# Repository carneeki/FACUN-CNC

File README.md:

# FACUN-CNC
It's not FANUC. It's FUCAN!

FUCAN CNC is a collection of circuits designed to enable connection of an
Arduino, probably running Grbl, to the "real world", that is, your stepper
controllers, limit switches, push buttons and pendants (if applicable), and so
on.

Developed by an impoverished university student, it is designed to be budget
conscious, whilst minimising compromises on things that are nice to have. One
example is that all logic components are in DIP form factor so they can be
socketed and easily replaced in the event that the magic smoke escapes a
component.

## TRI-LIMIT-INTERFACE
TRI-LIMIT-INTERFACE is a 3 axis limit switch debounce and logical OR board.
Because we often have limit switches at each end of our axis limits, this
handles debouncing both ends, and sending a single clean signal to the Arduino.

Grbl has some debounce routines in it, but having this board enables changing to
other systems that may not have debouncing built in.

## LIMIT-INTERFACE
LIMIT-INTERFACE is a single axis, strip board version of the 3 axis board. Not
everyone can fab a PCB, and not everyone can afford to have the large 3 axis
board professionally fabbed. The strip board version can be easily made (and
tripled) while getting started. Once you are up and running, you should be able
to route the TRI version if you are so inclined.

## PUSHBUTTON-DEBOUNCE
PUSHBUTTON-DEBOUNCE is a board for debouncing pushbutton switches.

## ArduinoMiniPro Breakout
The Arduino Mini Pro is a really neat little board. It takes an Arduino and puts
it into a wide DIP array.

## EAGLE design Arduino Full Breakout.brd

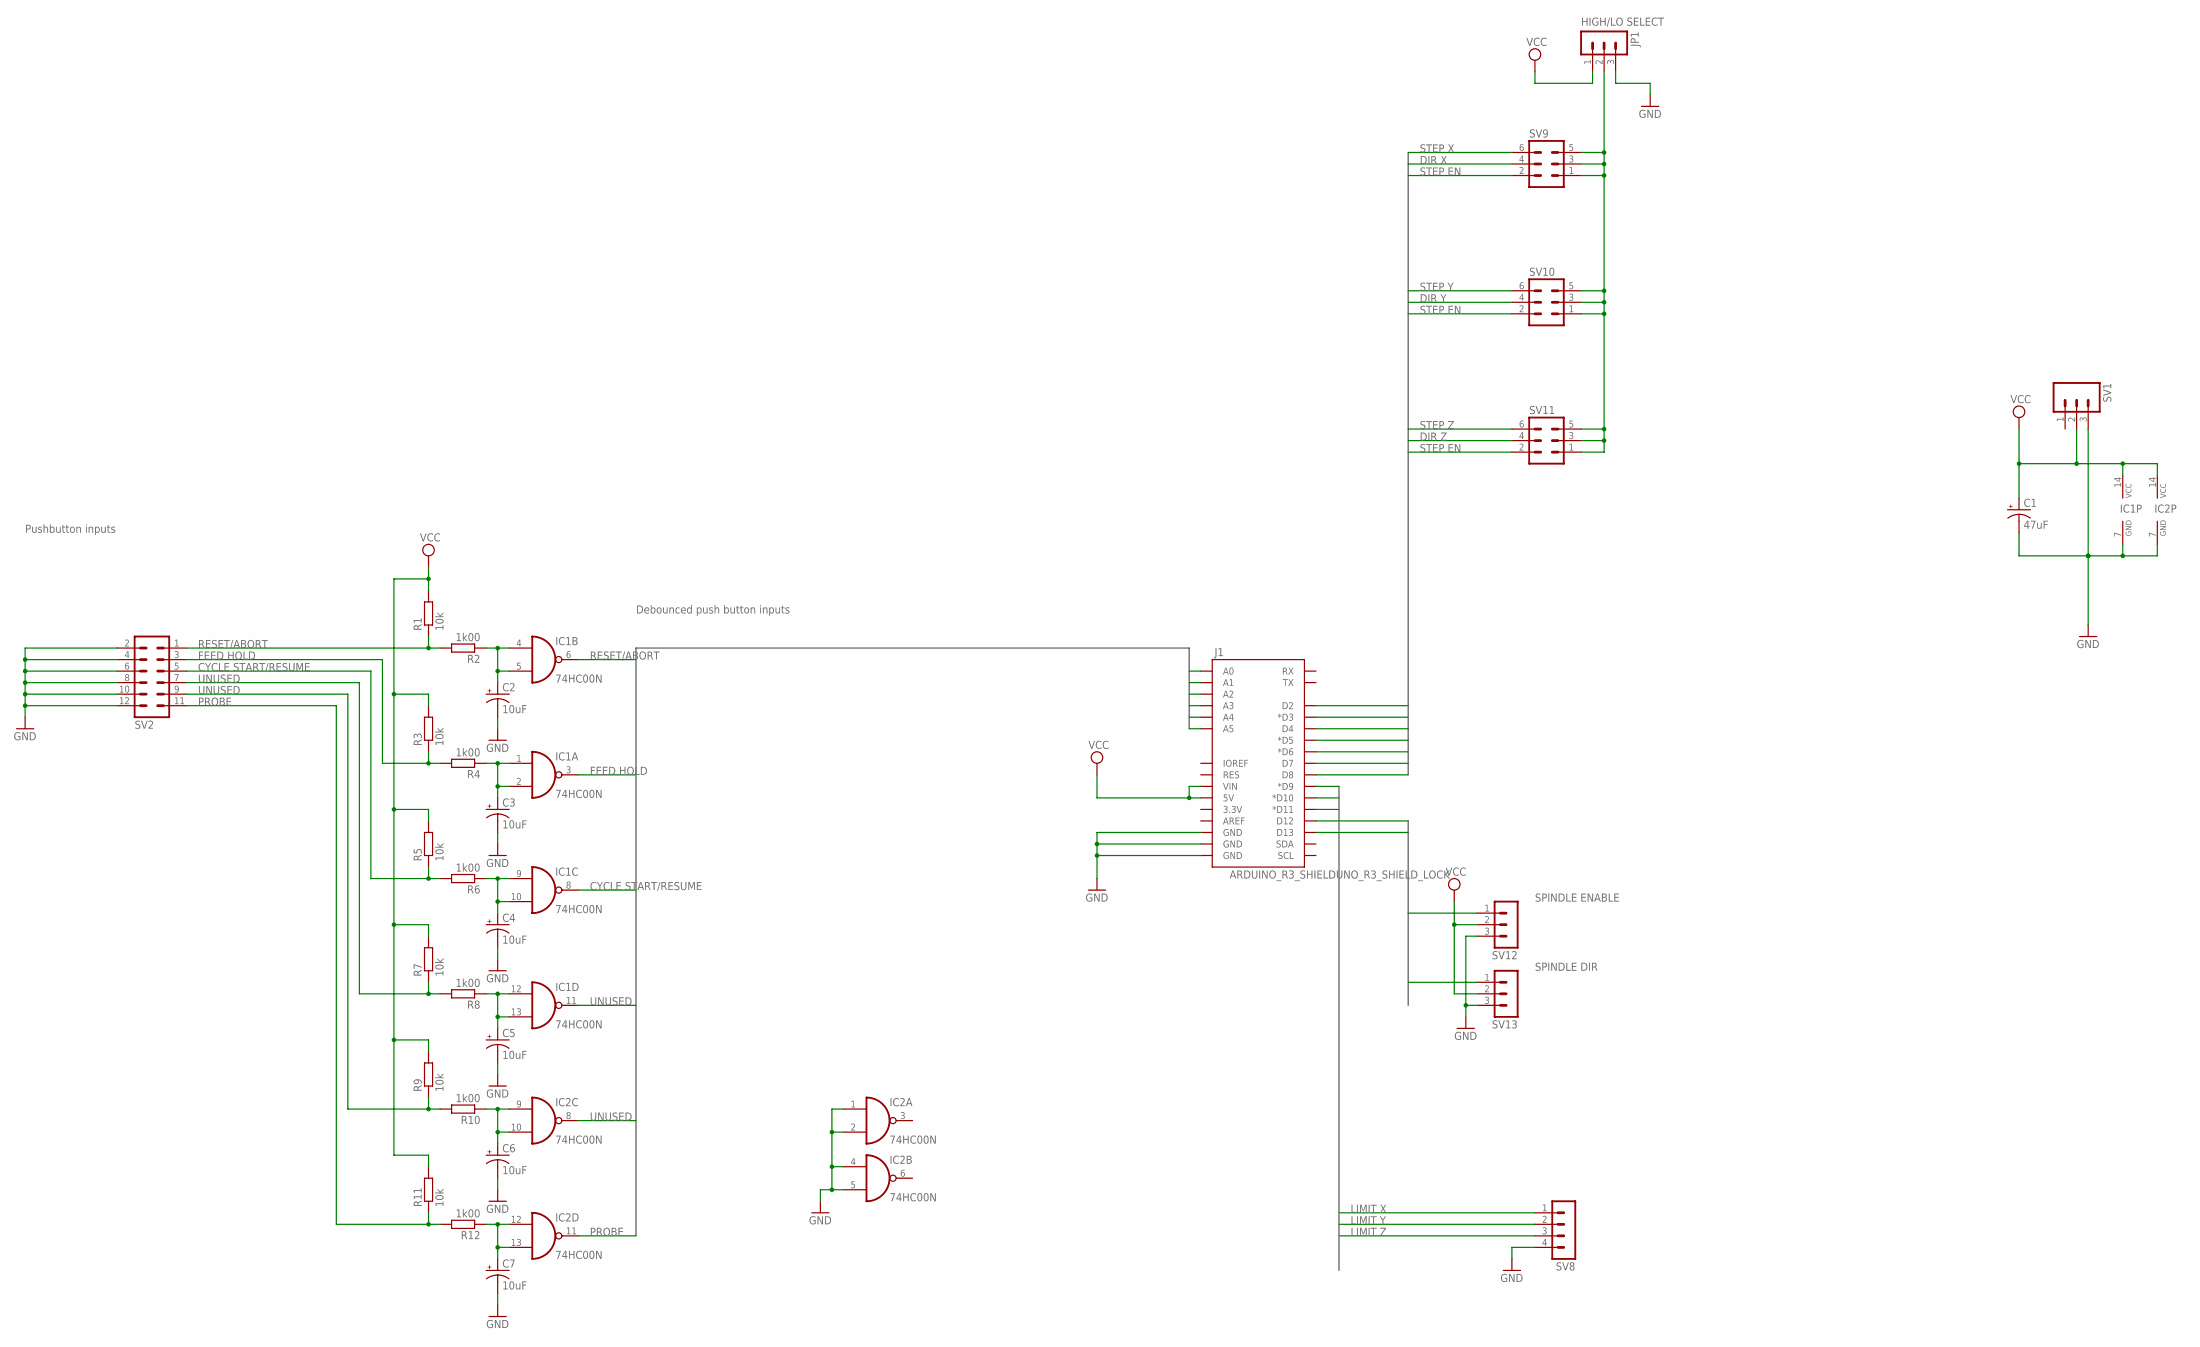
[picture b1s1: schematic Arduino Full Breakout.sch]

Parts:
C1: 47uF; CPOL-RADIAL-10UF-25V
C2, C3, C4, C5, C6, C7: 10uF; CPOL-RADIAL-10UF-25V
IC1, IC2: 74HC00N; DIL14
J1: ARDUINO_R3_SHIELDUNO_R3_SHIELD_LOCK; UNO_R3_SHIELD_LOCK
JP1: MA03-1
R1, R11: 10k; 0207/5V
R2, R4, R6, R8, R10, R12: 1k00; 0207/7
R3, R9: 10k; 0207/7
R5, R7: 10k; 0207/10
SV1: M03-SCREW-5MM; SCREWTERMINAL-5MM-3
SV2: MA06-2
SV8: MA04-1
SV9, SV10, SV11: MA03-2
SV12, SV13: MA03-1

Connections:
BUTTONS0: IC1.6 (O), J1.A0
BUTTONS1: IC1.3 (O), J1.A1
BUTTONS2: IC1.8 (O), J1.A2
BUTTONS3: IC1.11 (O), J1.A3
BUTTONS4: IC2.8 (O), J1.A4
BUTTONS5: IC2.11 (O), J1.A5
GND: C1.2 (-), C2.2 (-), C3.2 (-), C4.2 (-), C5.2 (-), C6.2 (-), C7.2 (-), IC1.7 (GND), IC2.1 (I0), IC2.2 (I1), IC2.4 (I0), IC2.5 (I1), IC2.7 (GND), J1.GND@0 (GND), J1.GND@1 (GND), J1.GND@2 (GND), JP1.3, SV1.3, SV2.2, SV2.4, SV2.6, SV2.8, SV2.10, SV2.12, SV8.4, SV12.3, SV13.3
LIMITS0: J1.D9 (*D9), SV8.1
LIMITS1: J1.D10 (*D10), SV8.2
LIMITS2: J1.D11 (*D11), SV8.3
unnamed: JP1.2, SV9.1, SV9.3, SV9.5, SV10.1, SV10.3, SV10.5, SV11.1, SV11.3, SV11.5
unnamed: C2.1 (+), IC1.4 (I0), IC1.5 (I1), R2.1
unnamed: R1.1, R2.2, SV2.1
unnamed: C3.1 (+), IC1.1 (I0), IC1.2 (I1), R4.1
unnamed: R3.1, R4.2, SV2.3
unnamed: C4.1 (+), IC1.9 (I0), IC1.10 (I1), R6.1
unnamed: R5.1, R6.2, SV2.5
unnamed: C5.1 (+), IC1.12 (I0), IC1.13 (I1), R8.1
unnamed: R7.1, R8.2, SV2.7
unnamed: C6.1 (+), IC2.9 (I0), IC2.10 (I1), R10.1
unnamed: R9.1, R10.2, SV2.9
unnamed: C7.1 (+), IC2.12 (I0), IC2.13 (I1), R12.1
unnamed: R11.1, R12.2, SV2.11
SPINDLE0: J1.D12, SV12.1
SPINDLE1: J1.D13, SV13.1
STEP0: J1.D2, SV9.6
STEP1: J1.D3 (*D3), SV10.6
STEP2: J1.D4, SV11.6
STEP3: J1.D5 (*D5), SV9.4
STEP4: J1.D6 (*D6), SV10.4
STEP5: J1.D7, SV11.4
STEP6: J1.D8, SV9.2, SV10.2, SV11.2
VCC: C1.1 (+), IC1.14 (VCC), IC2.14 (VCC), J1.VIN, JP1.1, R1.2, R3.2, R5.2, R7.2, R9.2, R11.2, SV1.2, SV12.2, SV13.2

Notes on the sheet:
RESET/ABORT
FEED HOLD
CYCLE START/RESUME
UNUSED
PROBE
SPINDLE DIR
SPINDLE ENABLE
LIMIT X
LIMIT Y
LIMIT Z
STEP X
STEP Y
HIGH/LO SELECT
DIR X
DIR Y
STEP Z
DIR Z
STEP EN
Debounced push button inputs
Pushbutton inputs

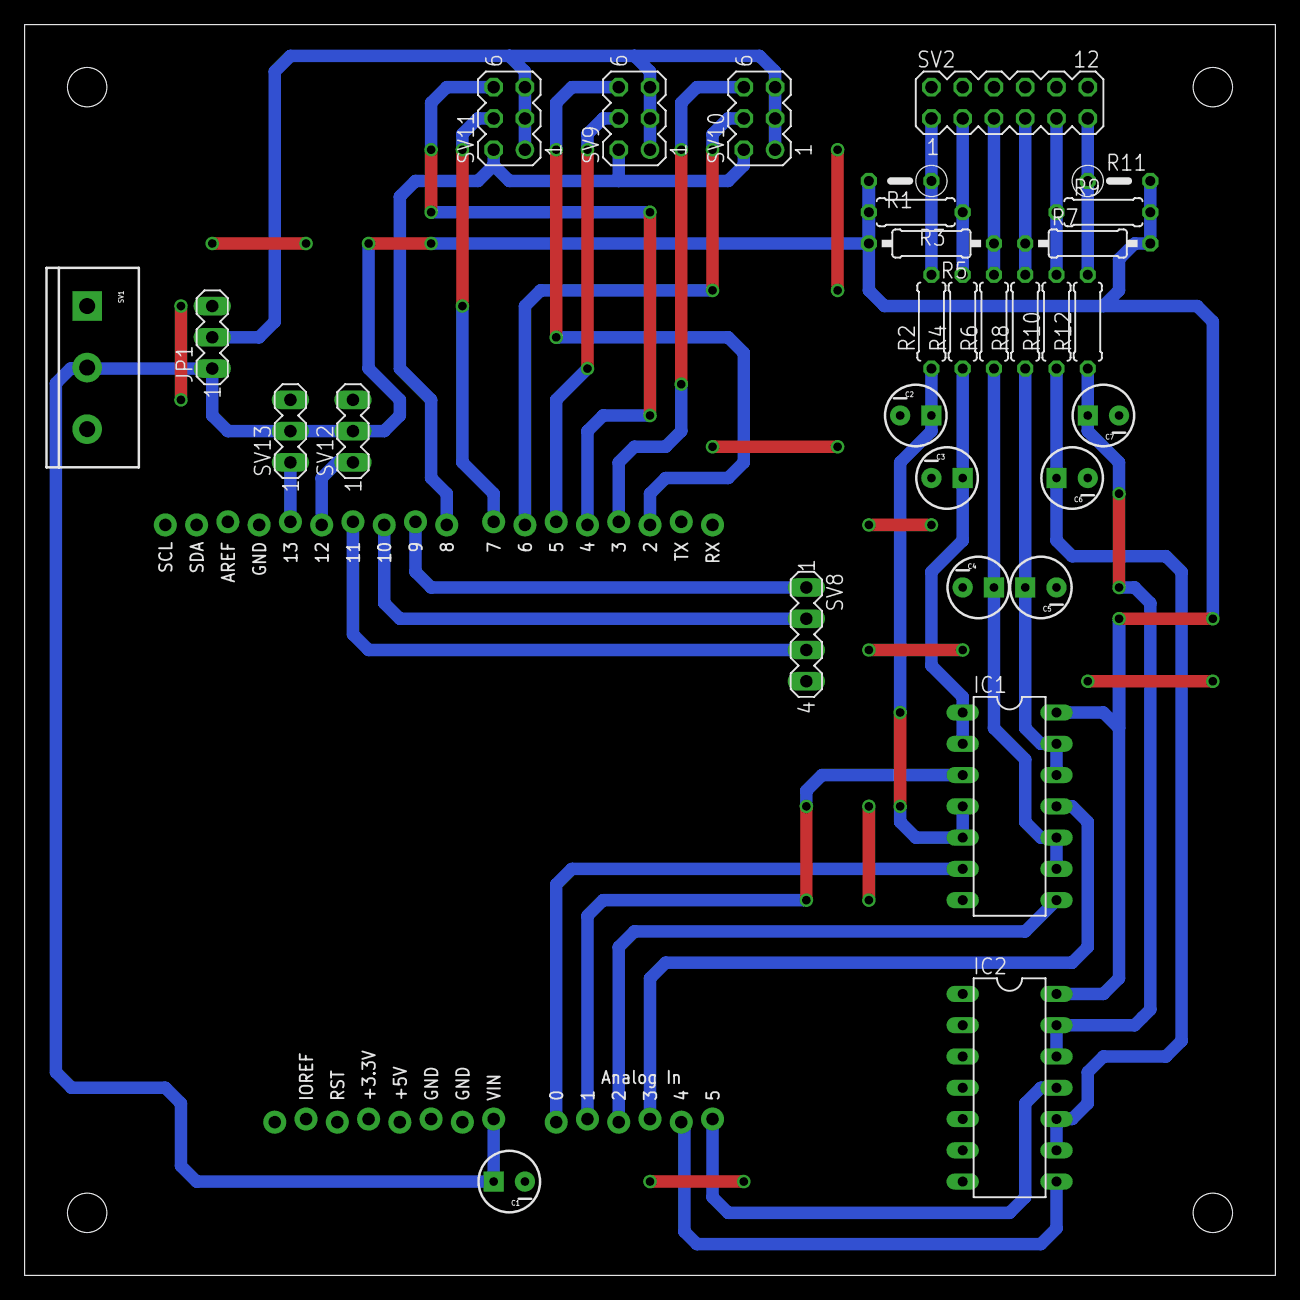
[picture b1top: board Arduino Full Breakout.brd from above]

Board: 2 copper layers, 101.6 x 101.6 mm, 31 parts (0 on the bottom side), 33 nets.

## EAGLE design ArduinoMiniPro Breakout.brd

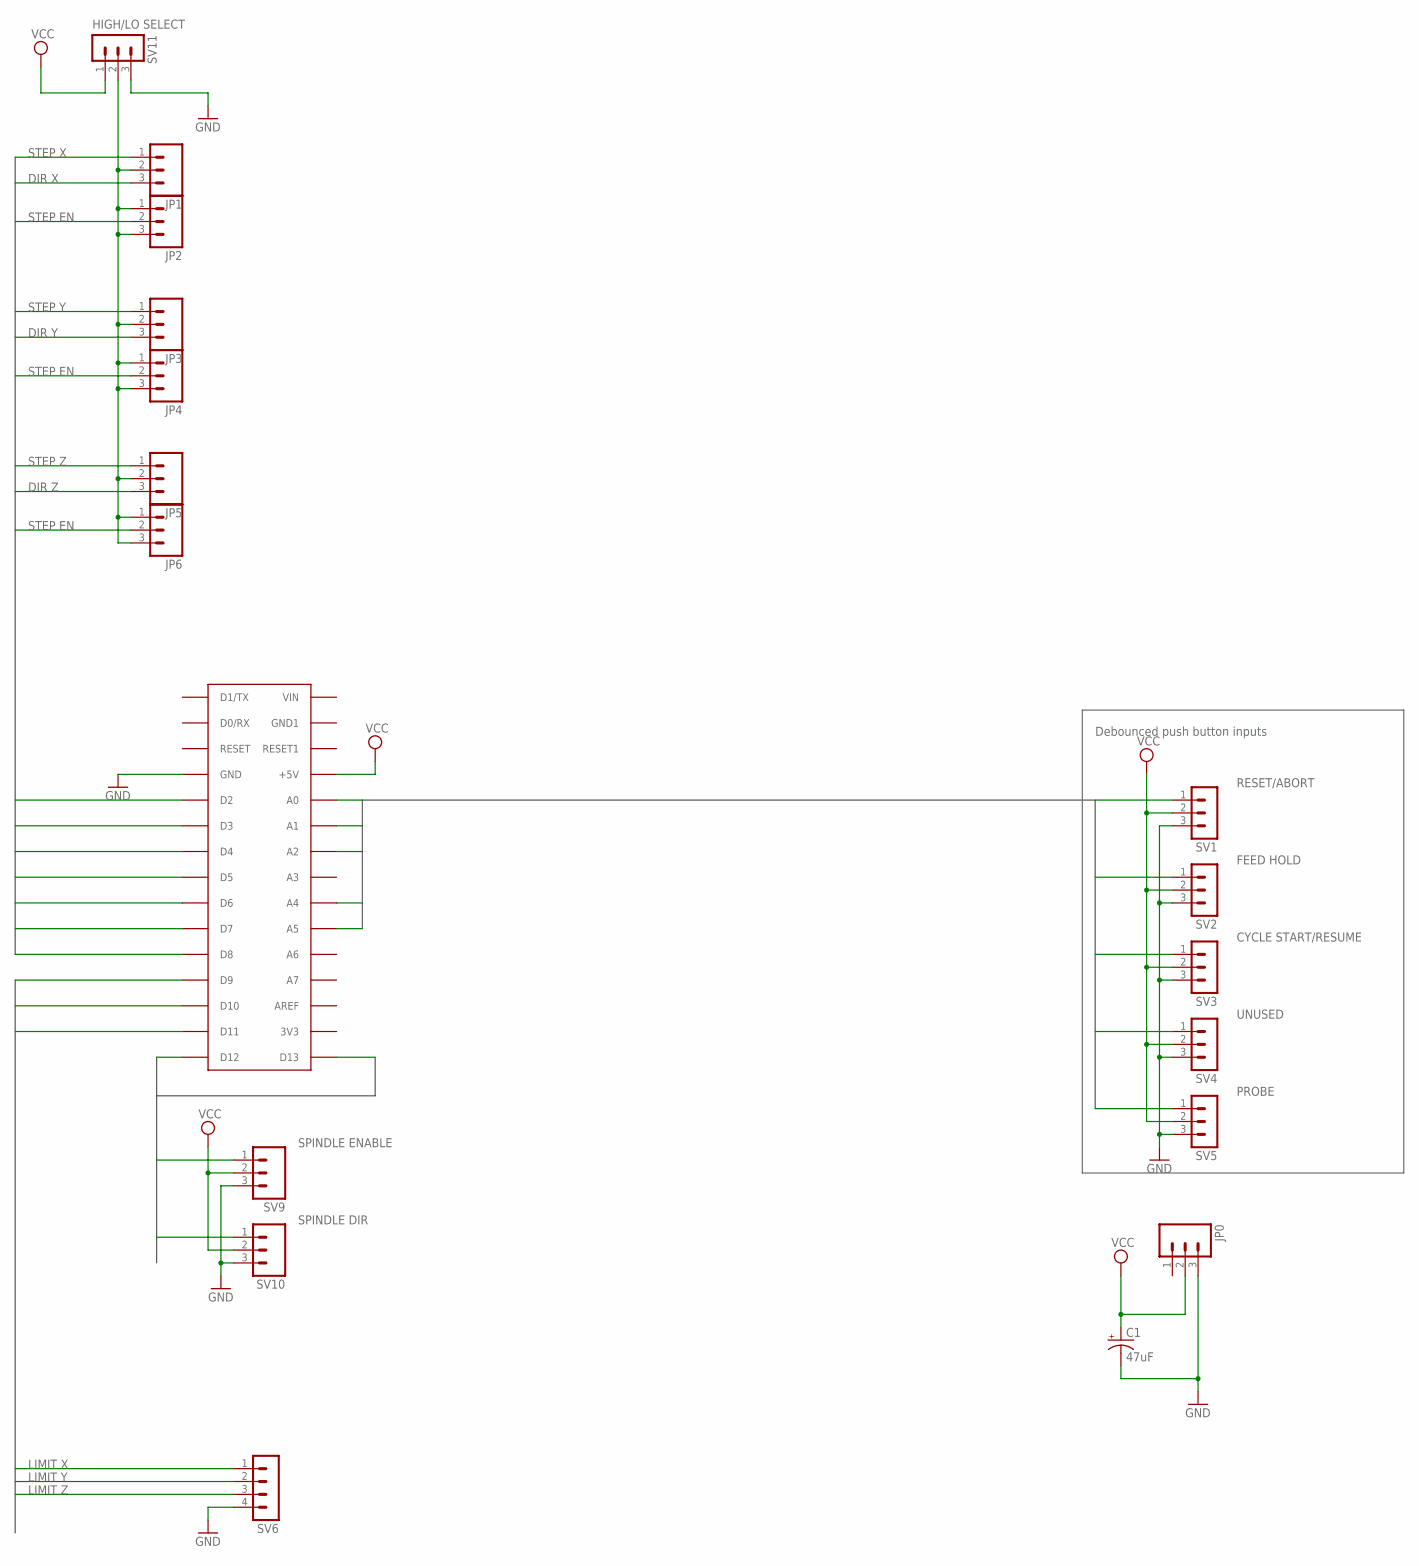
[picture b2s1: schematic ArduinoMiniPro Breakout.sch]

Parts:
C1: 47uF; CPOL-RADIAL-10UF-25V
JP0, JP1, JP2, JP3, JP4, JP5, JP6: M03-SCREW-5MM; SCREWTERMINAL-5MM-3
SV1, SV2, SV3, SV4, SV5, SV11: MA03-1
SV6: MA04-1
SV9, SV10: M03-SCREW-5MM; SCREWTERMINAL-5MM-3
U$2: ARDUINONANO; PDIP-32

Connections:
B0: SV1.1, U$2.A0
B1: SV2.1, U$2.A1
B2: SV3.1, U$2.A2
B4: SV4.1, U$2.A4
B5: SV5.1, U$2.A5
GND: C1.2 (-), JP0.3, SV1.3, SV2.3, SV3.3, SV4.3, SV5.3, SV6.4, SV9.3, SV10.3, SV11.3, U$2.GND
LIMITS0: SV6.1, U$2.D9
LIMITS1: SV6.2, U$2.D10
LIMITS2: SV6.3, U$2.D11
unnamed: JP1.2, JP2.1, JP2.3, JP3.2, JP4.1, JP4.3, JP5.2, JP6.1, JP6.3, SV11.2
SPINDLE0: SV9.1, U$2.D12
SPINDLE1: SV10.1, U$2.D13
STEP0: JP1.1, U$2.D2
STEP1: JP3.1, U$2.D3
STEP2: JP5.1, U$2.D4
STEP3: JP1.3, U$2.D5
STEP4: JP3.3, U$2.D6
STEP5: JP5.3, U$2.D7
STEP6: JP2.2, JP4.2, JP6.2, U$2.D8
VCC: C1.1 (+), JP0.2, SV1.2, SV2.2, SV3.2, SV4.2, SV5.2, SV9.2, SV10.2, SV11.1, U$2.+5V

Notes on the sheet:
RESET/ABORT
FEED HOLD
CYCLE START/RESUME
UNUSED
PROBE
SPINDLE DIR
SPINDLE ENABLE
LIMIT X
LIMIT Y
LIMIT Z
STEP X
STEP Y
HIGH/LO SELECT
DIR X
DIR Y
STEP Z
DIR Z
STEP EN
Debounced push button inputs

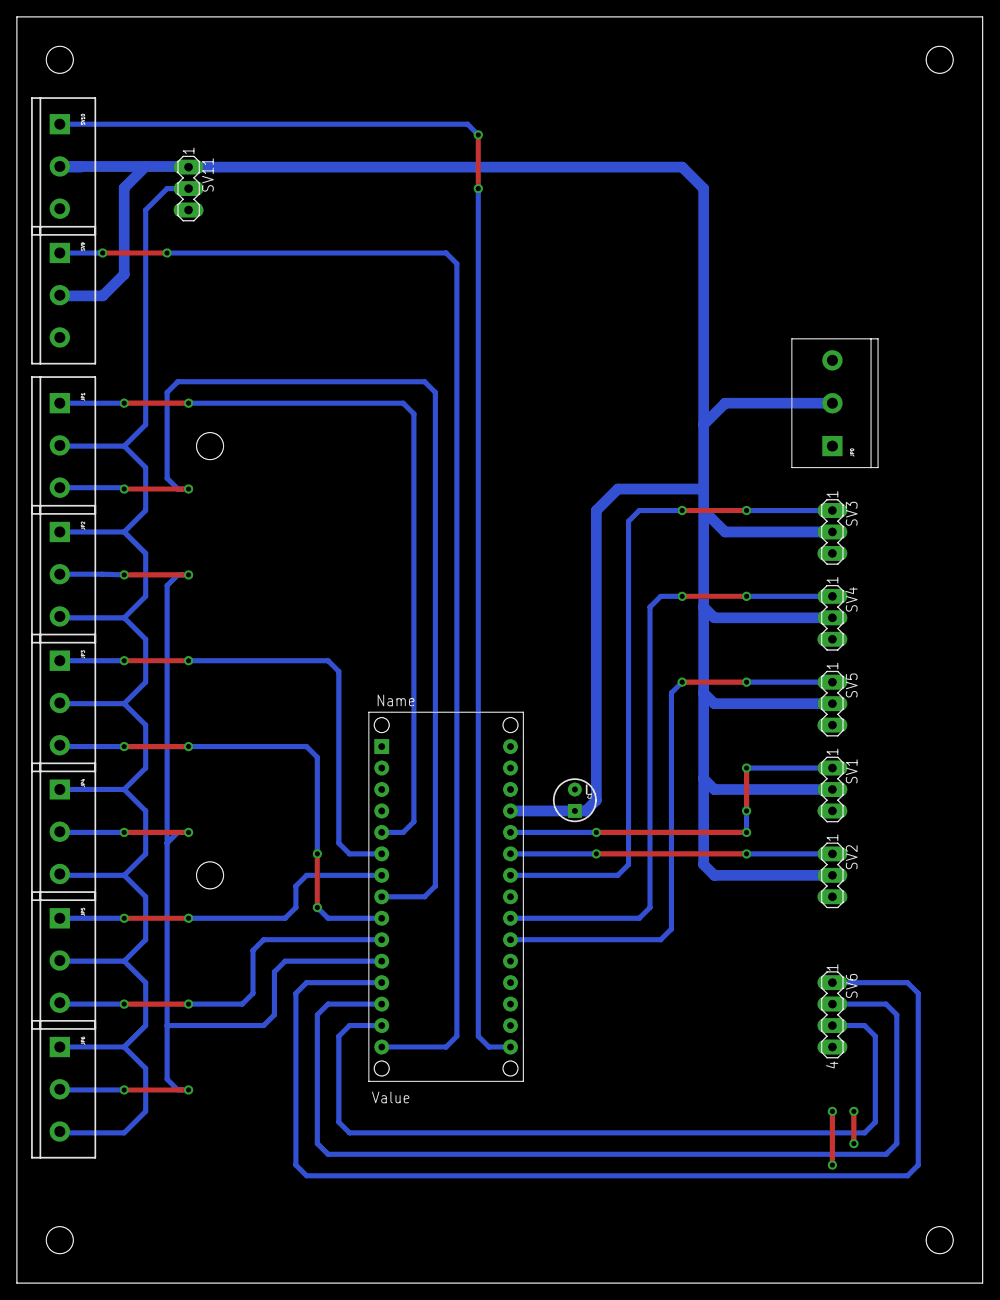
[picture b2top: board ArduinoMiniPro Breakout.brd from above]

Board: 2 copper layers, 114.3 x 149.9 mm, 18 parts (0 on the bottom side), 20 nets.

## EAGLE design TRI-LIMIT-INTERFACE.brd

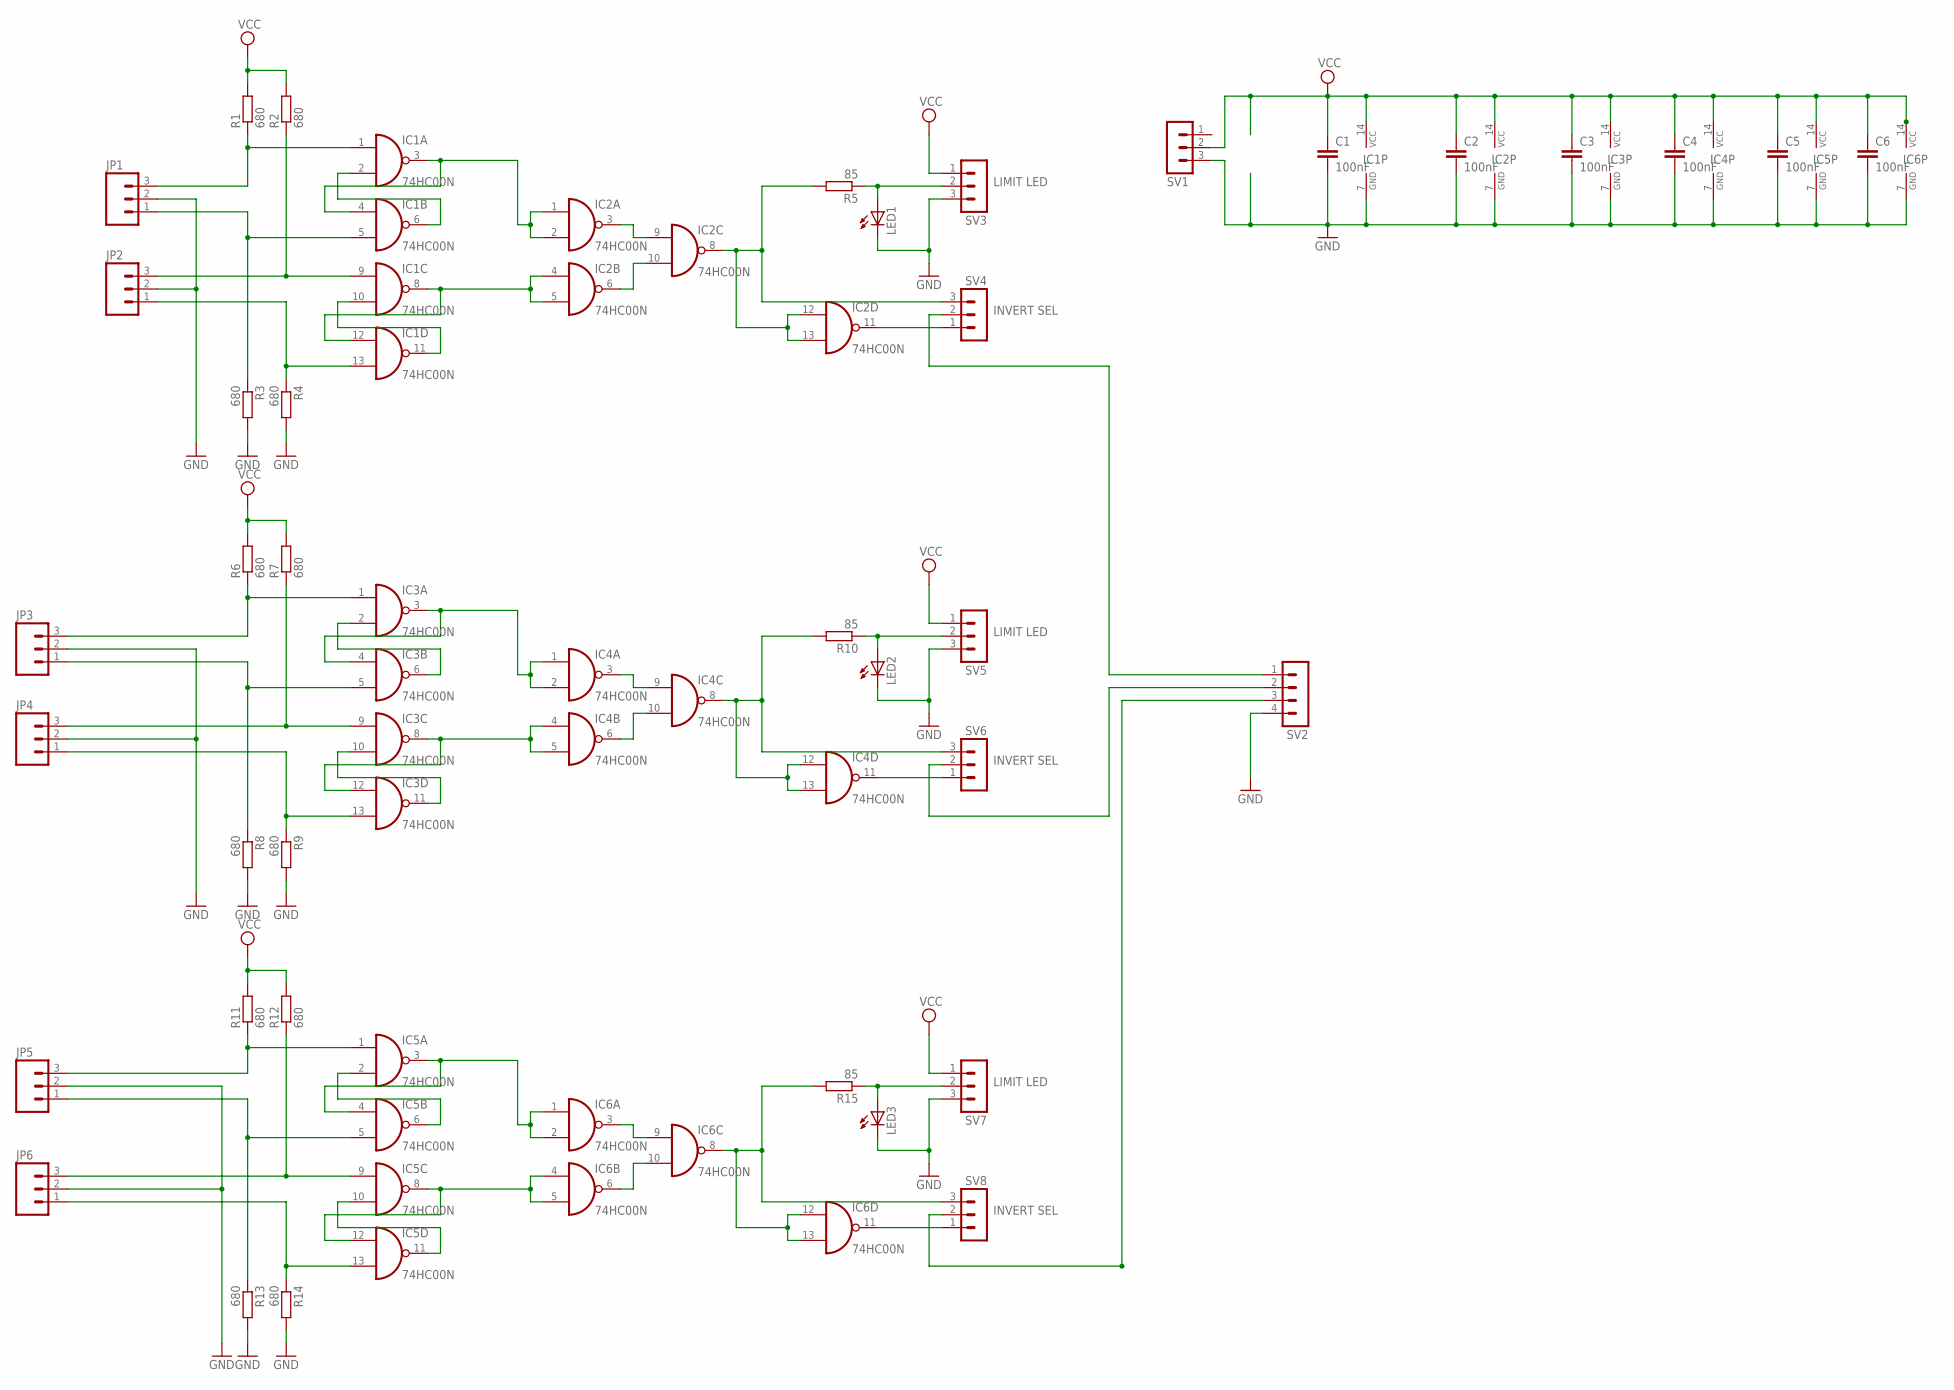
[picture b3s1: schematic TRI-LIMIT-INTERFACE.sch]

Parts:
C1, C2, C3, C4, C5, C6: 100nF; CAP-PTH-SMALL
IC1, IC2, IC3, IC4, IC5, IC6: 74HC00N; DIL14
JP1, JP2, JP3, JP4, JP5, JP6: M03-SCREW-5MM; SCREWTERMINAL-5MM-3
LED1, LED2, LED3: LED3MM
R1, R2, R3, R4, R6, R7, R8, R9, R11, R12, R13, R14: 680; 0207/7
R5, R10, R15: 85; 0207/10
SV1, SV3, SV4, SV5, SV6, SV7, SV8: MA03-1
SV2: MA04-1

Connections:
/SIG: IC2.11 (O), SV4.1
/SIG1: IC4.11 (O), SV6.1
/SIG2: IC6.11 (O), SV8.1
GND: C1.2, C2.2, C3.2, C4.2, C5.2, C6.2, IC1.7 (GND), IC2.7 (GND), IC3.7 (GND), IC4.7 (GND), IC5.7 (GND), IC6.7 (GND), JP1.2, JP2.2, JP3.2, JP4.2, JP5.2, JP6.2, LED1.K (C), LED2.K (C), LED3.K (C), R3.2, R4.2, R8.2, R9.2, R13.2, R14.2, SV1.3, SV2.4, SV3.3, SV5.3, SV7.3
unnamed: IC1.3 (O), IC1.4 (I0), IC2.1 (I0), IC2.2 (I1)
unnamed: IC1.2 (I1), IC1.6 (O)
unnamed: IC1.13 (I1), JP2.1, R4.1
unnamed: IC1.5 (I1), JP1.1, R3.1
unnamed: IC1.8 (O), IC1.12 (I0), IC2.4 (I0), IC2.5 (I1)
unnamed: IC1.10 (I1), IC1.11 (O)
unnamed: IC1.9 (I0), JP2.3, R2.1
unnamed: IC1.1 (I0), JP1.3, R1.1
unnamed: IC2.3 (O), IC2.9 (I0)
unnamed: IC2.6 (O), IC2.10 (I1)
unnamed: IC3.3 (O), IC3.4 (I0), IC4.1 (I0), IC4.2 (I1)
unnamed: IC3.2 (I1), IC3.6 (O)
unnamed: IC3.1 (I0), JP3.3, R6.1
unnamed: IC3.5 (I1), JP3.1, R8.1
unnamed: IC3.8 (O), IC3.12 (I0), IC4.4 (I0), IC4.5 (I1)
unnamed: LED1.A, R5.1, SV3.2
unnamed: IC3.10 (I1), IC3.11 (O)
unnamed: IC3.9 (I0), JP4.3, R7.1
unnamed: IC3.13 (I1), JP4.1, R9.1
unnamed: IC4.3 (O), IC4.9 (I0)
unnamed: IC4.6 (O), IC4.10 (I1)
unnamed: LED2.A, R10.1, SV5.2
unnamed: IC5.3 (O), IC5.4 (I0), IC6.1 (I0), IC6.2 (I1)
unnamed: IC5.2 (I1), IC5.6 (O)
unnamed: IC5.1 (I0), JP5.3, R11.1
unnamed: IC5.5 (I1), JP5.1, R13.1
unnamed: IC5.8 (O), IC5.12 (I0), IC6.4 (I0), IC6.5 (I1)
unnamed: IC5.10 (I1), IC5.11 (O)
unnamed: IC5.9 (I0), JP6.3, R12.1
unnamed: IC5.13 (I1), JP6.1, R14.1
unnamed: IC6.3 (O), IC6.9 (I0)
unnamed: IC6.6 (O), IC6.10 (I1)
unnamed: LED3.A, R15.1, SV7.2
SIG: IC2.8 (O), IC2.12 (I0), IC2.13 (I1), R5.2, SV4.3
SIG1: IC4.8 (O), IC4.12 (I0), IC4.13 (I1), R10.2, SV6.3
SIG2: IC6.8 (O), IC6.12 (I0), IC6.13 (I1), R15.2, SV8.3
TO_CPU0: SV2.1, SV4.2
TO_CPU1: SV2.2, SV6.2
TO_CPU2: SV2.3, SV8.2
VCC: C1.1, C2.1, C3.1, C4.1, C5.1, C6.1, IC1.14 (VCC), IC2.14 (VCC), IC3.14 (VCC), IC4.14 (VCC), IC5.14 (VCC), IC6.14 (VCC), R1.2, R2.2, R6.2, R7.2, R11.2, R12.2, SV1.2, SV3.1, SV5.1, SV7.1

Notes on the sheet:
INVERT SEL
LIMIT LED

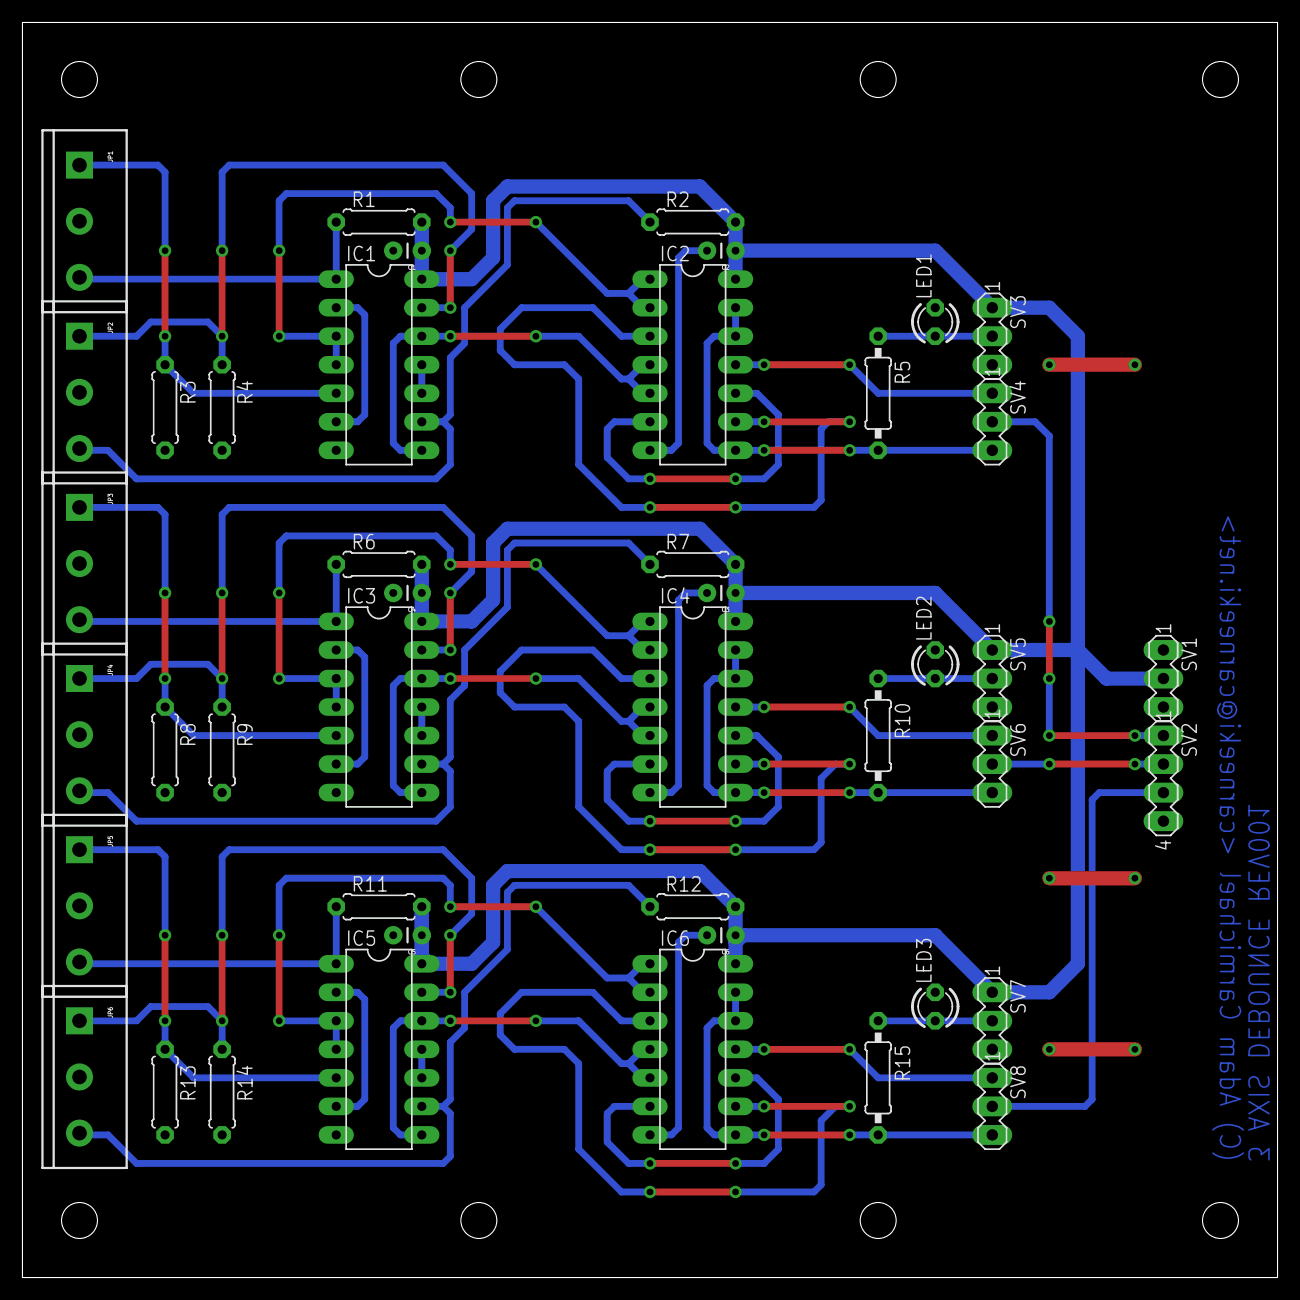
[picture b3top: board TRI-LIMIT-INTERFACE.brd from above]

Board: 2 copper layers, 111.8 x 111.8 mm, 44 parts (0 on the bottom side), 44 nets.

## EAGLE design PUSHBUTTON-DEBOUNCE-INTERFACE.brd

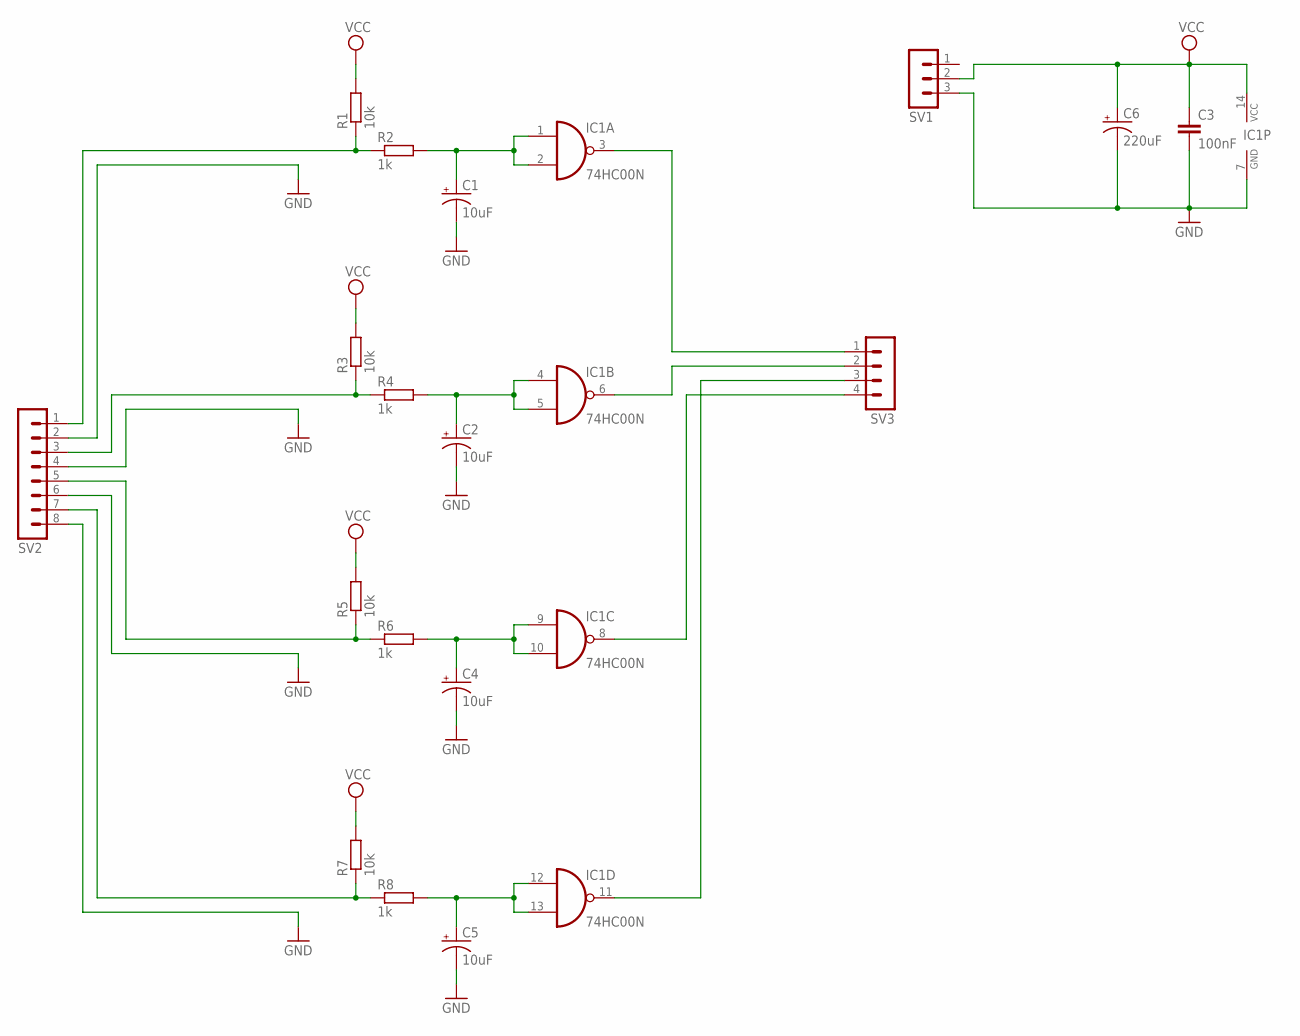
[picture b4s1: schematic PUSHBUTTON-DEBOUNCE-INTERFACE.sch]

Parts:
C1, C2, C4, C5: 10uF; CPOL-RADIAL-100UF-25V
C3: 100nF; CAP-PTH-SMALL
C6: 220uF; CPOL-RADIAL-1000UF-25V
IC1: 74HC00N; DIL14
R1, R7: 10k; 0207/7
R2, R4, R6, R8: 1k; 0207/7
R3, R5: 10k; 0207/12
SV1: MA03-1
SV2: MA08-1
SV3: MA04-1

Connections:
GND: C1.2 (-), C2.2 (-), C3.2, C4.2 (-), C5.2 (-), C6.2 (-), IC1.7 (GND), SV1.3, SV2.2, SV2.4, SV2.6, SV2.8
unnamed: C1.1 (+), IC1.1 (I0), IC1.2 (I1), R2.2
unnamed: C2.1 (+), IC1.4 (I0), IC1.5 (I1), R4.2
unnamed: C4.1 (+), IC1.9 (I0), IC1.10 (I1), R6.2
unnamed: C5.1 (+), IC1.12 (I0), IC1.13 (I1), R8.2
unnamed: IC1.3 (O), SV3.1
unnamed: IC1.6 (O), SV3.2
unnamed: IC1.8 (O), SV3.4
unnamed: IC1.11 (O), SV3.3
unnamed: R1.1, R2.1, SV2.1
unnamed: R3.1, R4.1, SV2.3
unnamed: R5.1, R6.1, SV2.5
unnamed: R7.1, R8.1, SV2.7
VCC: C3.1, C6.1 (+), IC1.14 (VCC), R1.2, R3.2, R5.2, R7.2, SV1.2

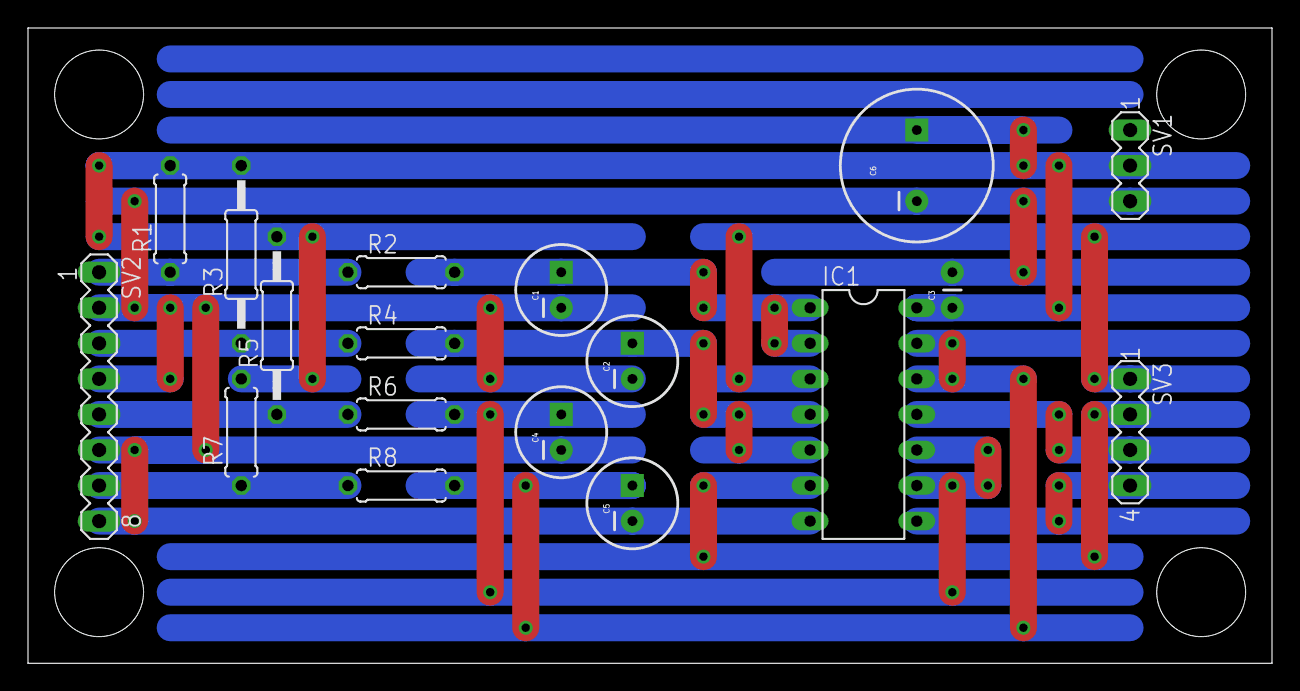
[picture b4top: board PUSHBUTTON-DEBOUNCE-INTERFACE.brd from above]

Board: 2 copper layers, 88.9 x 45.4 mm, 18 parts (0 on the bottom side), 14 nets.

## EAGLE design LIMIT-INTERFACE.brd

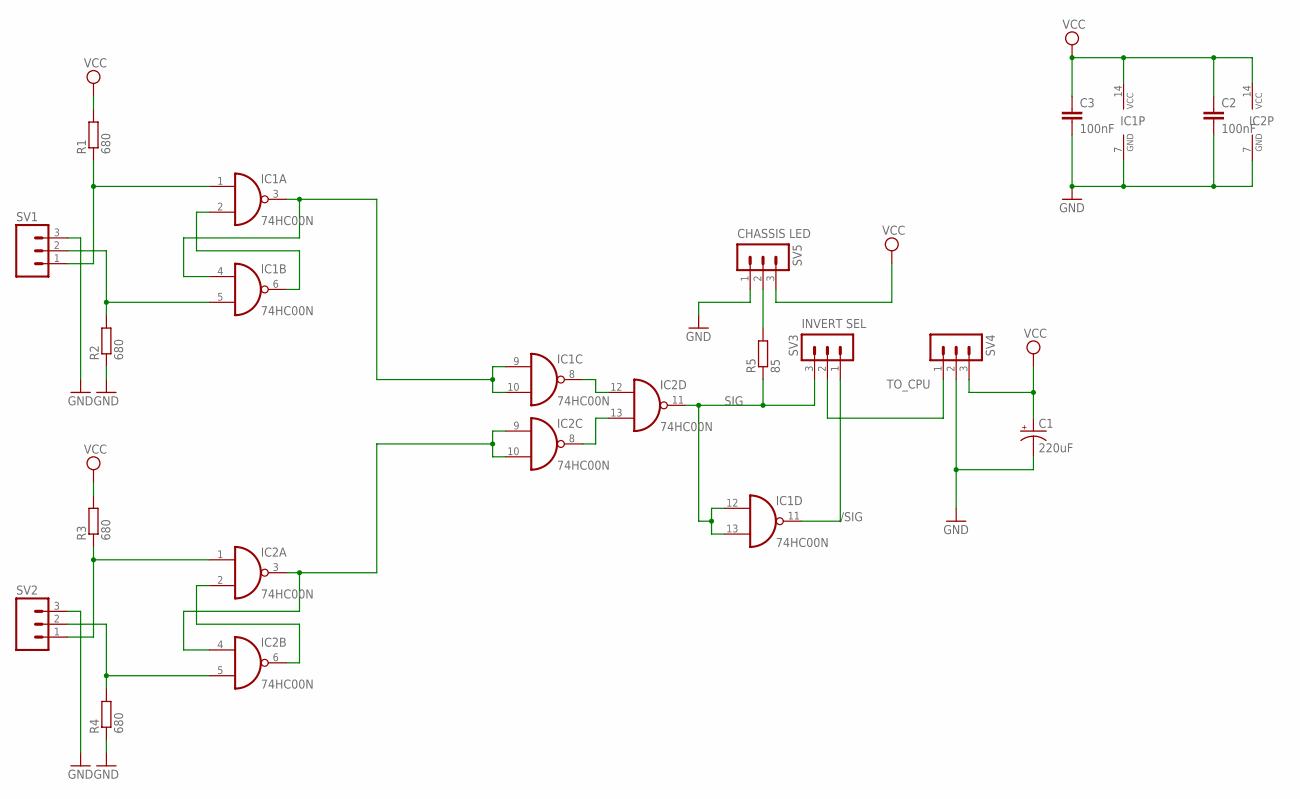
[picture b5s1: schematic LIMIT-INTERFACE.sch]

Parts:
C1: 220uF; CPOL-RADIAL-1000UF-25V
C2, C3: 100nF; CAP-PTH-SMALL
IC1, IC2: 74HC00N; DIL14
R1, R3: 680; 0207/7
R2, R4: 680; 0207/5V
R5: 85; 0207/10
SV1, SV2: M03-SCREW-5MM; SCREWTERMINAL-5MM-3
SV3, SV4, SV5: MA03-1

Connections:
/SIG: IC1.11 (O), SV3.1
GND: C1.2 (-), C2.2, C3.2, IC1.7 (GND), IC2.7 (GND), R2.1, R4.1, SV1.3, SV2.3, SV4.2, SV5.1
unnamed: IC1.3 (O), IC1.4 (I0), IC1.9 (I0), IC1.10 (I1)
unnamed: IC1.2 (I1), IC1.6 (O)
unnamed: IC1.1 (I0), R1.1, SV1.1
unnamed: IC1.5 (I1), R2.2, SV1.2
unnamed: IC2.3 (O), IC2.4 (I0), IC2.9 (I0), IC2.10 (I1)
unnamed: IC2.2 (I1), IC2.6 (O)
unnamed: IC2.1 (I0), R3.1, SV2.1
unnamed: IC2.5 (I1), R4.2, SV2.2
unnamed: IC1.8 (O), IC2.12 (I0)
unnamed: IC2.8 (O), IC2.13 (I1)
unnamed: R5.2, SV5.2
SIG: IC1.12 (I0), IC1.13 (I1), IC2.11 (O), R5.1, SV3.3
TO_CPU: SV3.2, SV4.1
VCC: C1.1 (+), C2.1, C3.1, IC1.14 (VCC), IC2.14 (VCC), R1.2, R3.2, SV4.3, SV5.3

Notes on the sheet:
INVERT SEL
CHASSIS LED

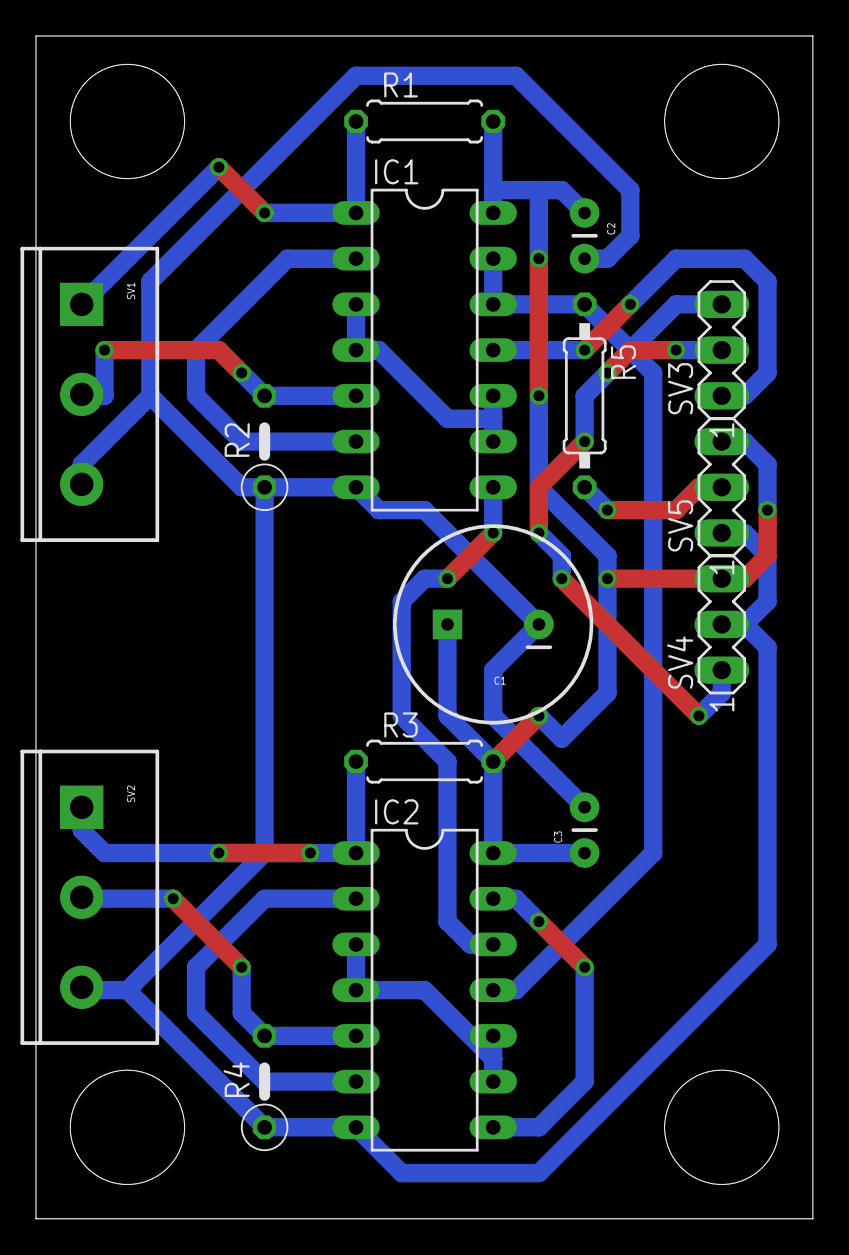
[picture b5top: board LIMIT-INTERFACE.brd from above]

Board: 2 copper layers, 43.2 x 65.7 mm, 15 parts (0 on the bottom side), 16 nets.

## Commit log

2015-04-05 gitignore
2015-04-05 commit the first bunch of files
2015-04-05 line endings
2015-04-05 modify readme
2015-04-05 Made the board a pure breakout board
    Rather than smooshing all the functions onto a single board, this board
    is purely for breaking out the pins to headers.
    Given the relatively large size, there is no reason a full size Arduino
    cannot be used, and so a full size breakout is on the way.
2015-04-05 Full size breakout board
    I'm not 100% happy with how this turned out. TODO: come up with a
    consistent board between both mini and full size Arduinos.
2015-04-06 Correct a heading level
2015-04-08 add pushbutton debounce to full size breakout board

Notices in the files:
parts and their libraries:
SparkFun-Passives: Licensing: Creative Commons ShareAlike 4.0 International - https://creativecommons.org/licenses/by-sa/4.0
